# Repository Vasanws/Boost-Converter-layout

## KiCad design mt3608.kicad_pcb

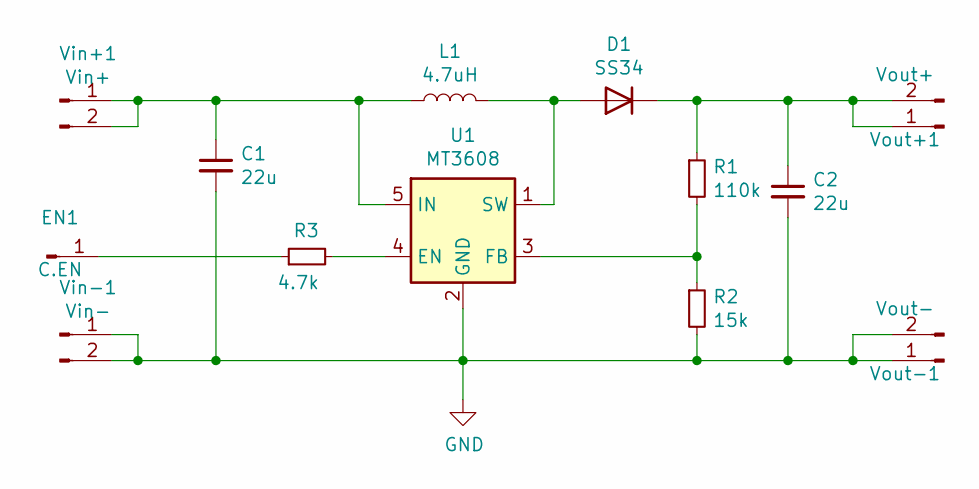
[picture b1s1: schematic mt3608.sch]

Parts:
C1, C2: 22u; C_0805_2012Metric_Pad1.18x1.45mm_HandSolder
D1: SS34; D_SMA
EN1: C.EN; PinHeader_1x01_P2.54mm_Vertical
L1: 4.7uH; L_Bourns-SRU1028_10.0x10.0mm
R1: 110k; R_0805_2012Metric_Pad1.20x1.40mm_HandSolder
R2: 15k; R_0805_2012Metric_Pad1.20x1.40mm_HandSolder
R3: 4.7k; R_0805_2012Metric_Pad1.20x1.40mm_HandSolder
U1: MT3608; SOT-23-6
Vin+1: Vin+; PinHeader_1x02_P2.54mm_Vertical
Vin-1: Vin-; PinHeader_1x02_P2.54mm_Vertical
Vout+1: Vout+; PinHeader_1x02_P2.54mm_Vertical
Vout-1: Vout-; PinHeader_1x02_P2.54mm_Vertical

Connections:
GND: C1.2, C2.2, R2.2, U1.2 (GND), Vin-1.1, Vin-1.2, Vout-1.1, Vout-1.2
unnamed: C1.1, L1.1, U1.5 (IN), Vin+1.1, Vin+1.2
unnamed: C2.1, D1.1 (K), R1.1, Vout+1.1, Vout+1.2
unnamed: D1.2 (A), L1.2, U1.1 (SW)
unnamed: EN1.1, R3.1
unnamed: R1.2, R2.1, U1.3 (FB)
unnamed: R3.2, U1.4 (EN)

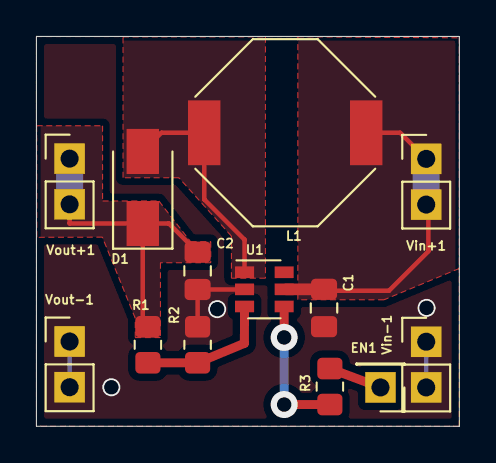
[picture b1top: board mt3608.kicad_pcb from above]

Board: 2 copper layers, 23.5 x 21.7 mm, 13 parts (0 on the bottom side), 7 nets.

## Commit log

2021-11-29 boost converter layout
